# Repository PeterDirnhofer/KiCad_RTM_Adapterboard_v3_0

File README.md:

# 500-rtm-kicad-controllerboard
KiCad files für das Controllerboard des 500Euro Raster Tunnel Mikroskop.

Beschreibung in https://500-euro-rtm.de/wiki/index.php?title=500-Euro-Rastertunnelmikroskop  

## Patches

<b><h3>3.0.1</h3> (19.01.2026)</b>
- Updated silkscreen description of RX/TX as they were swapped before.  
- Plotted new gerber / drill files and added .zip  
- Updated versioning to 3.0.1 on kicad file  
- Removed versioning from image files to avoid confusion. Also fixed RX/TX there.

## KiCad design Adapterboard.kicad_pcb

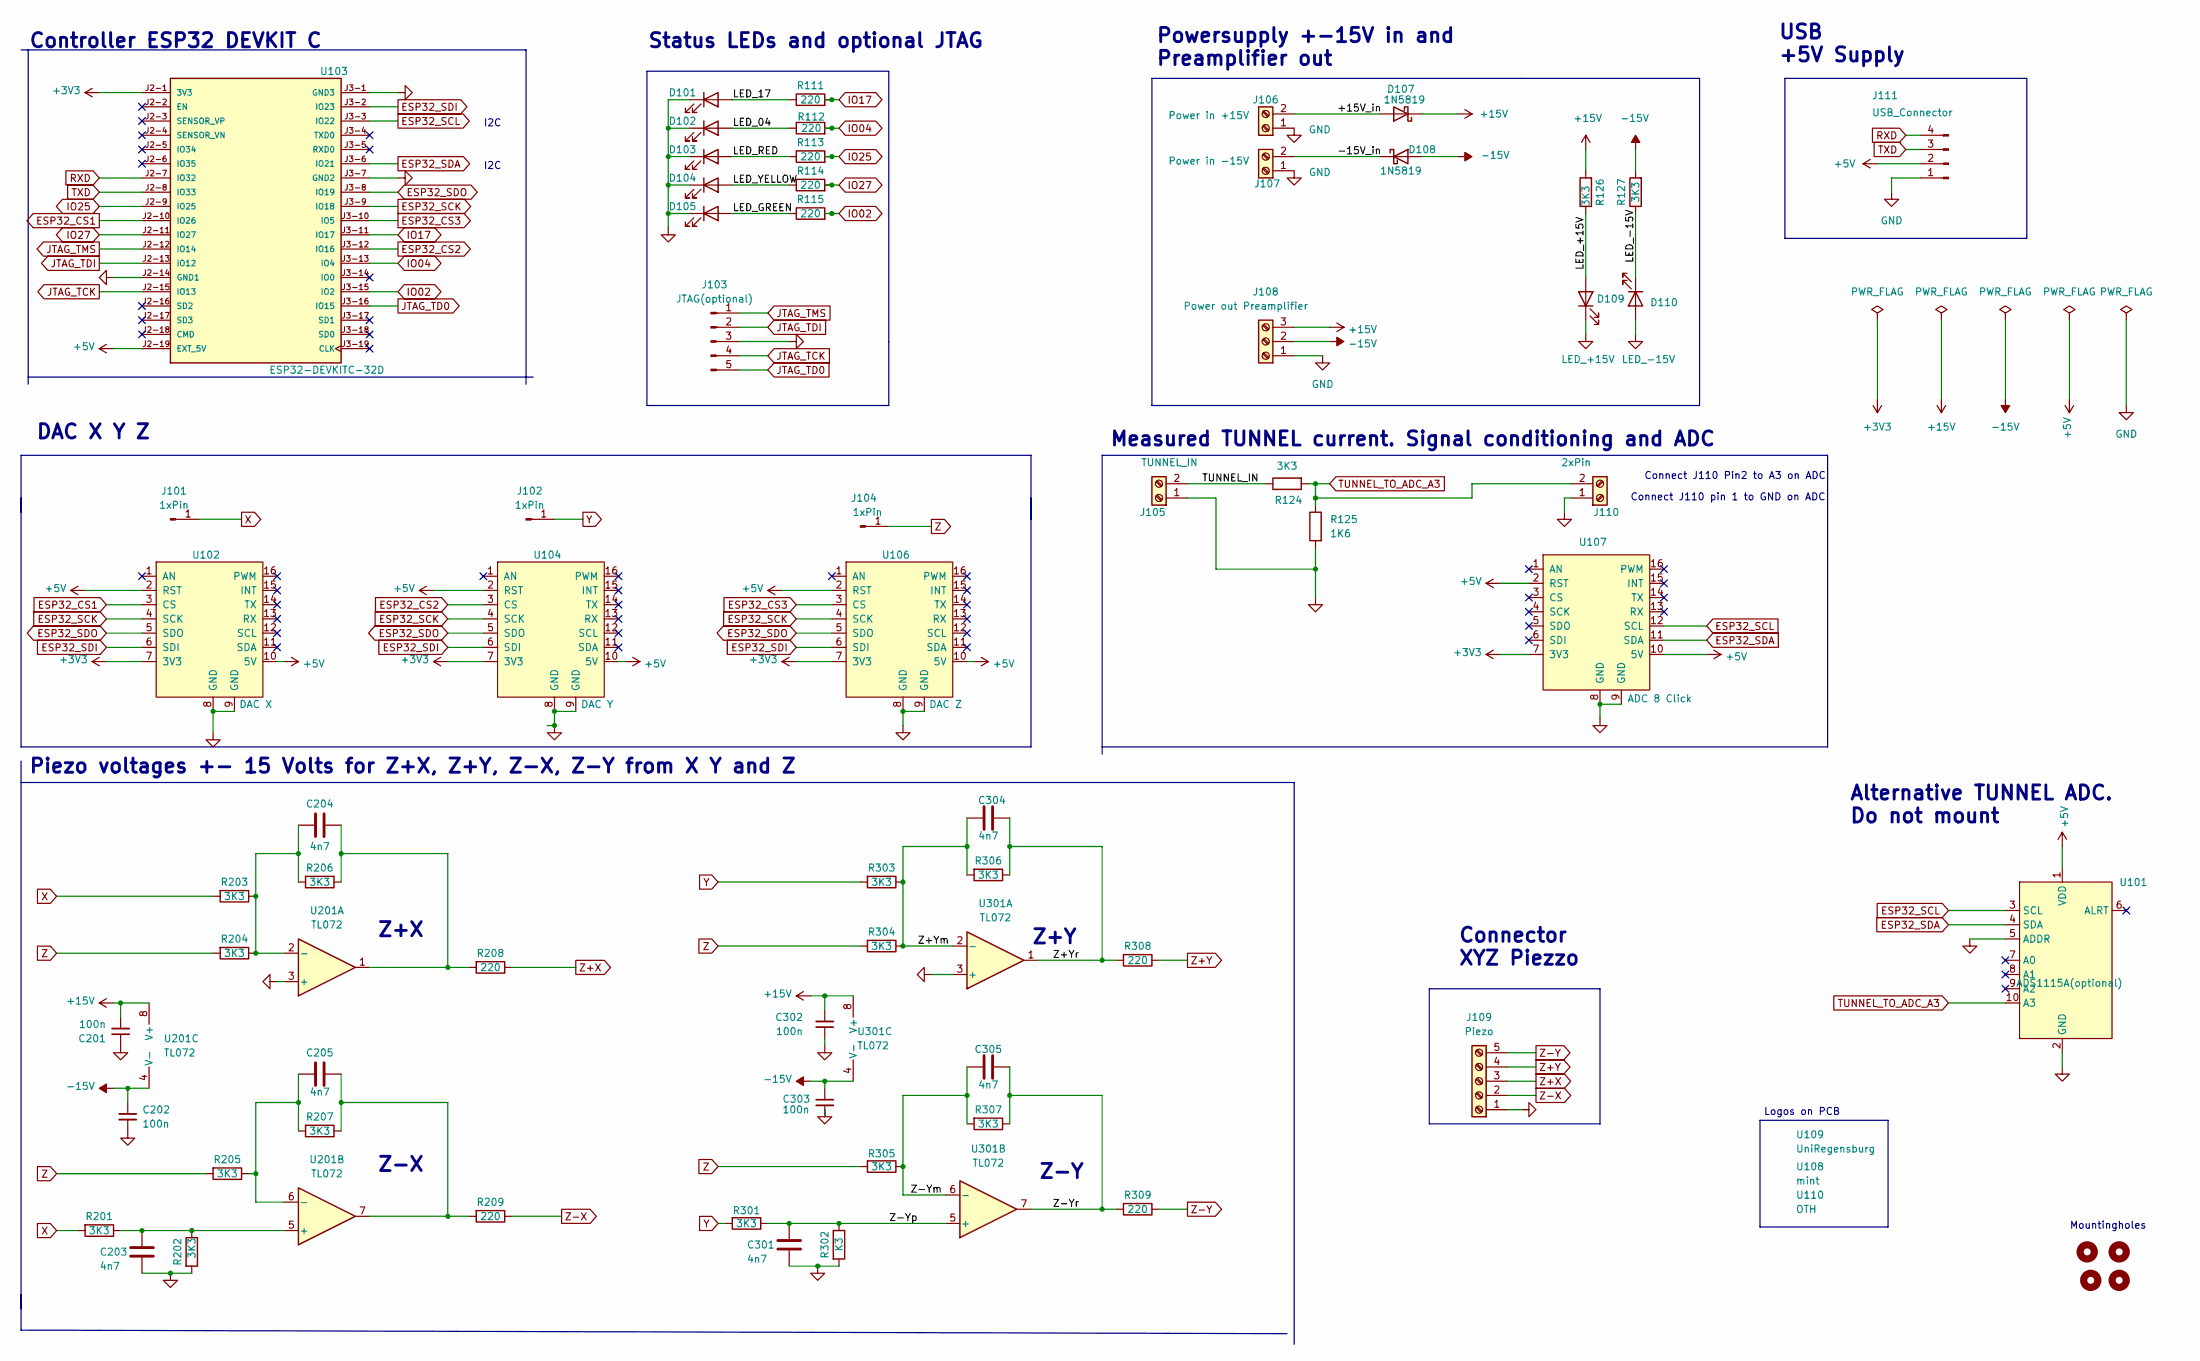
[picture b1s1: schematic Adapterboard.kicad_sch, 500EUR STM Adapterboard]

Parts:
C201, C202, C302, C303: 100n; C_Disc_D5.0mm_W2.5mm_P2.50mm
C203, C204, C205, C301, C304, C305: 4n7; C_Disc_D5.0mm_W2.5mm_P2.50mm
D101, D102: LED; LED_D3.0mm_Clear
D103: RED; LED_D3.0mm_Clear
D104: YELLOW; LED_D3.0mm_Clear
D105: GREEN; LED_D3.0mm_Clear
D107, D108: 1N5819; D_DO-41_SOD81_P10.16mm_Horizontal
D109: LED_+15V; LED_D3.0mm_Clear
D110: LED_-15V; LED_D3.0mm_Clear
H101, H102, H103, H104: MountingHole; MountingHole_3.2mm_M3
J101, J102, J104: 1xPin; PinHeader_1x01_P2.54mm_Vertical
J103: JTAG(optional); PinHeader_1x05_P2.54mm_Vertical
J105: TUNNEL_IN; TerminalBlock_Xinya_XY308-2.54-2P_1x02_P2.54mm_Horizontal
J106: Power in +15V; TerminalBlock_Xinya_XY308-2.54-2P_1x02_P2.54mm_Horizontal
J107: Power in -15V; TerminalBlock_Xinya_XY308-2.54-2P_1x02_P2.54mm_Horizontal
J108: Power out Preamplifier; TerminalBlock_Xinya_XY308-2.54-3P_1x03_P2.54mm_Horizontal
J109: Piezo; TerminalBlock_Xinya_XY308-2.54-5P_1x05_P2.54mm_Horizontal
J110: 2xPin; PinHeader_1x02_P2.54mm_Vertical
J111: USB_Connector; PinHeader_1x04_P2.54mm_Vertical
R111, R112, R113, R114, R115, R208, R209, R308, R309: 220; R_Axial_DIN0207_L6.3mm_D2.5mm_P10.16mm_Horizontal
R124, R126, R127, R201, R202, R203, R204, R205, R206, R207, R301, R303, R304, R305, R306, R307: 3K3; R_Axial_DIN0207_L6.3mm_D2.5mm_P10.16mm_Horizontal
R125: 1K6; R_Axial_DIN0207_L6.3mm_D2.5mm_P10.16mm_Horizontal
R302: K3; R_Axial_DIN0207_L6.3mm_D2.5mm_P10.16mm_Horizontal
U101: ADS1115A(optional); PinHeader_1x10_P2.54mm_Vertical
U102: DAC X; Mikroe_Socket_DAC_2_Click
U103: ESP32-DEVKITC-32D; MODULE_ESP32-DEVKITC-32D; PARTREV V4
U104: DAC Y; Mikroe_Socket_DAC_2_Click
U106: DAC Z; Mikroe_Socket_DAC_2_Click
U107: ADC 8 Click; Mikroe_Socket_ADC_8_Click
U108: mint
U109: UniRegensburg; ur
U110: OTH; oth
U201, U301: TL072; DIP-8_W7.62mm

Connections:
+3V3: U102.7 (3V3), U103.J2-1 (3V3), U104.7 (3V3), U106.7 (3V3), U107.7 (3V3)
+5V: J111.2, U101.1 (VDD), U102.2 (RST), U102.10 (5V), U103.J2-19 (EXT_5V), U104.2 (RST), U104.10 (5V), U106.2 (RST), U106.10 (5V), U107.2 (RST), U107.10 (5V)
+15V: C201.2, C302.2, D107.1 (K), J108.3, R126.2, U201.8 (V+), U301.8 (V+)
-15V: C202.1, C303.1, D108.2 (A), J108.2, R127.2, U201.4 (V-), U301.4 (V-)
/+15V_in: D107.2 (A), J106.2
/-15V_in: D108.1 (K), J107.2
/LED_04: D102.2 (A), R112.1
/LED_17: D101.2 (A), R111.1
/LED_+15V: D109.2 (A), R126.1
/LED_-15V: D110.1 (K), R127.1
/LED_GREEN: D105.2 (A), R115.1
/LED_RED: D103.2 (A), R113.1
/LED_YELLOW: D104.2 (A), R114.1
/TUNNEL_IN: J105.2, R124.1
/Z+Ym: C304.2, R303.1, R304.1, R306.2, U301.2 (-)
/Z+Yr: C304.1, R306.1, R308.2, U301.1
/Z-Ym: C305.2, R305.1, R307.2, U301.6 (-)
/Z-Yp: C301.1, R301.1, R302.1, U301.5 (+)
/Z-Yr: C305.1, R307.1, R309.2, U301.7
ESP32_CS1: U102.3 (CS), U103.J2-10 (IO26)
ESP32_CS2: U103.J3-12 (IO16), U104.3 (CS)
ESP32_CS3: U103.J3-10 (IO5), U106.3 (CS)
ESP32_SCK: U102.4 (SCK), U103.J3-9 (IO18), U104.4 (SCK), U106.4 (SCK)
ESP32_SCL: U101.3 (SCL), U103.J3-3 (IO22), U107.12 (SCL)
ESP32_SDA: U101.4 (SDA), U103.J3-6 (IO21), U107.11 (SDA)
ESP32_SDI: U102.6 (SDI), U103.J3-2 (IO23), U104.6 (SDI), U106.6 (SDI)
ESP32_SDO: U102.5 (SDO), U103.J3-8 (IO19), U104.5 (SDO), U106.5 (SDO)
GND: C201.1, C202.2, C203.2, C301.2, C302.1, C303.2, D101.1 (K), D102.1 (K), D103.1 (K), D104.1 (K), D105.1 (K), D109.1 (K), D110.2 (A), J103.3, J105.1, J106.1, J107.1, J108.1, J109.1, J110.1, J111.1, R125.2, R202.2, R302.2, U101.2 (GND), U101.5 (ADDR), U102.8 (GND), U102.9 (GND), U103.J2-14 (GND1), U103.J3-1 (GND3), U103.J3-7 (GND2), U104.8 (GND), U104.9 (GND), U106.8 (GND), U106.9 (GND), U107.8 (GND), U107.9 (GND), U201.3 (+), U301.3 (+)
IO02: R115.2, U103.J3-15 (IO2)
IO04: R112.2, U103.J3-13 (IO4)
IO17: R111.2, U103.J3-11 (IO17)
IO25: R113.2, U103.J2-9 (IO25)
IO27: R114.2, U103.J2-11 (IO27)
JTAG_TCK: J103.4, U103.J2-15 (IO13)
JTAG_TD0: J103.5, U103.J3-16 (IO15)
JTAG_TDI: J103.2, U103.J2-13 (IO12)
JTAG_TMS: J103.1, U103.J2-12 (IO14)
unnamed: C204.1, R206.1, R208.2, U201.1
unnamed: C205.1, R207.1, R209.2, U201.7
unnamed: C204.2, R203.1, R204.1, R206.2, U201.2 (-)
unnamed: C203.1, R201.1, R202.1, U201.5 (+)
unnamed: C205.2, R205.1, R207.2, U201.6 (-)
RXD: J111.4, U103.J2-7 (IO32)
TUNNEL_TO_ADC_A3: J110.2, R124.2, R125.1, U101.10 (A3)
TXD: J111.3, U103.J2-8 (IO33)
X: J101.1, R201.2, R203.2
Y: J102.1, R301.2, R303.2
Z: J104.1, R204.2, R205.2, R304.2, R305.2
Z+X: J109.3, R208.1
Z+Y: J109.4, R308.1
Z-X: J109.2, R209.1
Z-Y: J109.5, R309.1

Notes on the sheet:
Measured TUNNEL current. Signal conditioning and ADC
Connector XYZ Piezzo
Status LEDs and optional JTAG
I2C
Z-Y
USB +5V Supply
Powersupply +-15V in and Preamplifier out
Controller ESP32 DEVKIT C
Connect J110 pin 1 to GND on ADC
Mountingholes
Piezo voltages +- 15 Volts for Z+X, Z+Y, Z-X, Z-Y from X Y and Z
Connect J110 Pin2 to A3 on ADC
Logos on PCB
DAC X Y Z
Alternative TUNNEL ADC. Do not mount
Z-X
Z+X
Z+Y

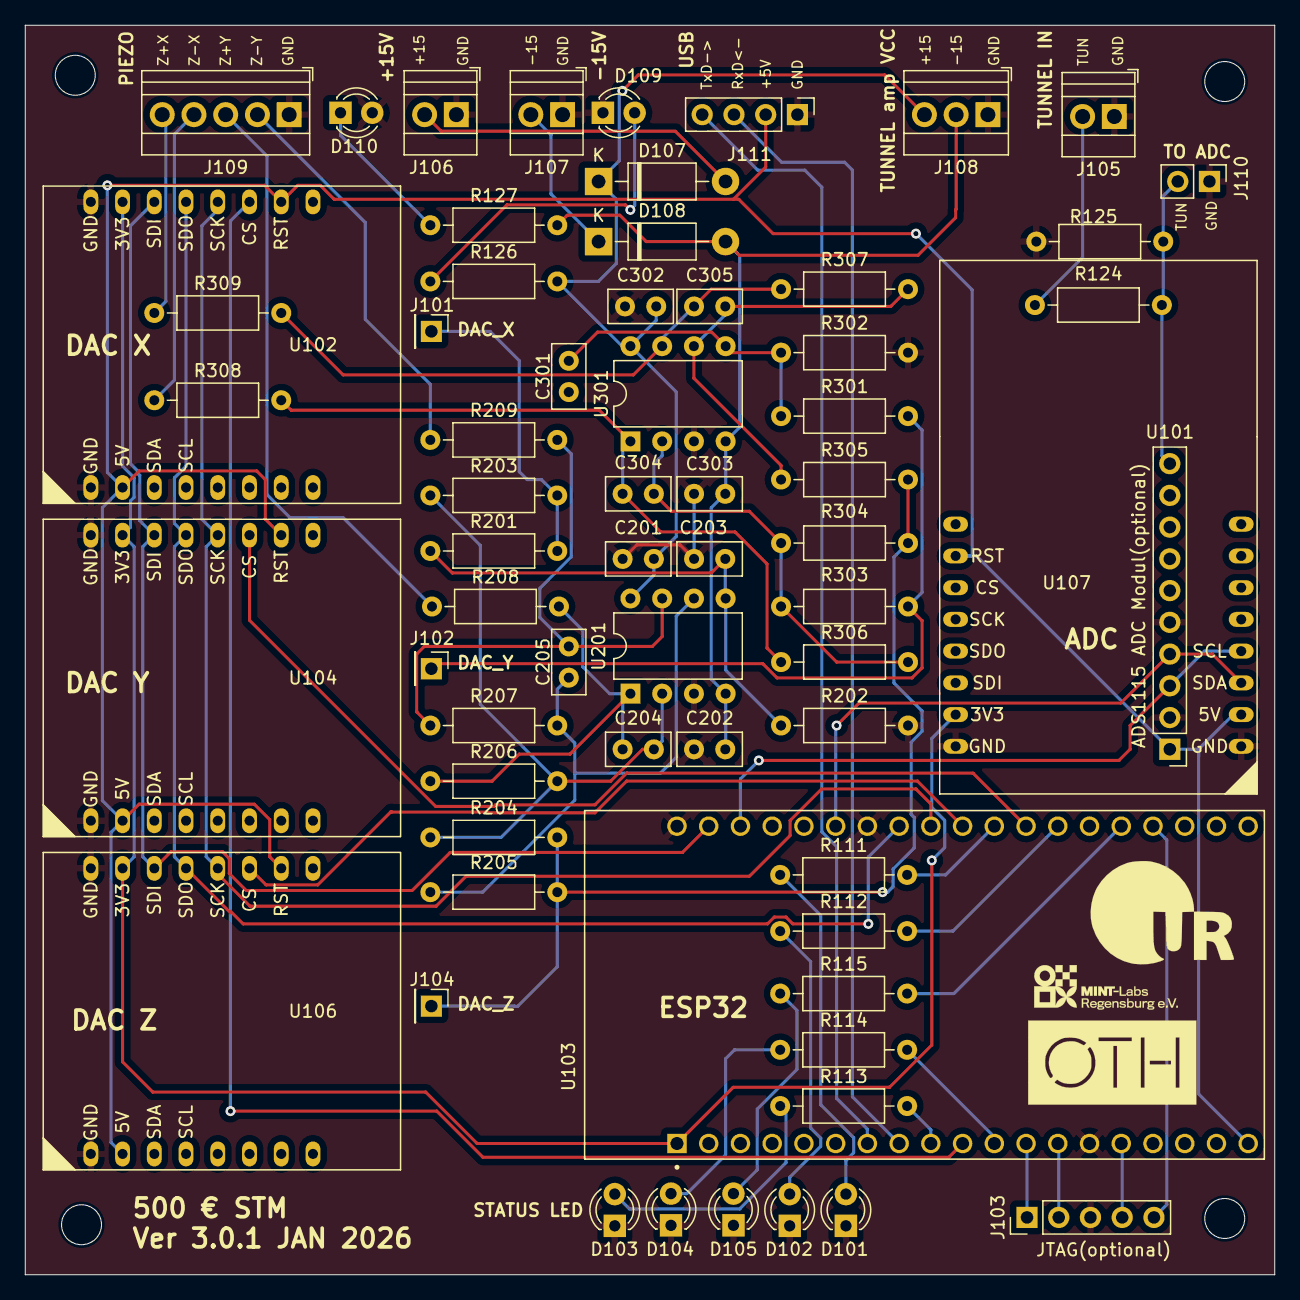
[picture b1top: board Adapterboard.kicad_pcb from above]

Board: 2 copper layers, 100.0 x 100.0 mm, 72 parts (0 on the bottom side), 52 nets.

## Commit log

2025-02-18 Initial commit of KiCad project
2025-02-18 pcb ready. add gnd
2025-02-20 pcb-supermarkt
2025-02-20 Bestellung Fischer 20250220
2026-01-19 Rx and Tx have been swapped. New Gerber files have been generated. Version number updated to 3.0.1 on gerber silkscreen file
2026-01-19 Added backup folder from 3.0. Added gerber files
2026-01-19 Updated kicad_pcb file.
2026-01-19 added readme info + patchnotes and removed temporary .lck data that prevented editing
